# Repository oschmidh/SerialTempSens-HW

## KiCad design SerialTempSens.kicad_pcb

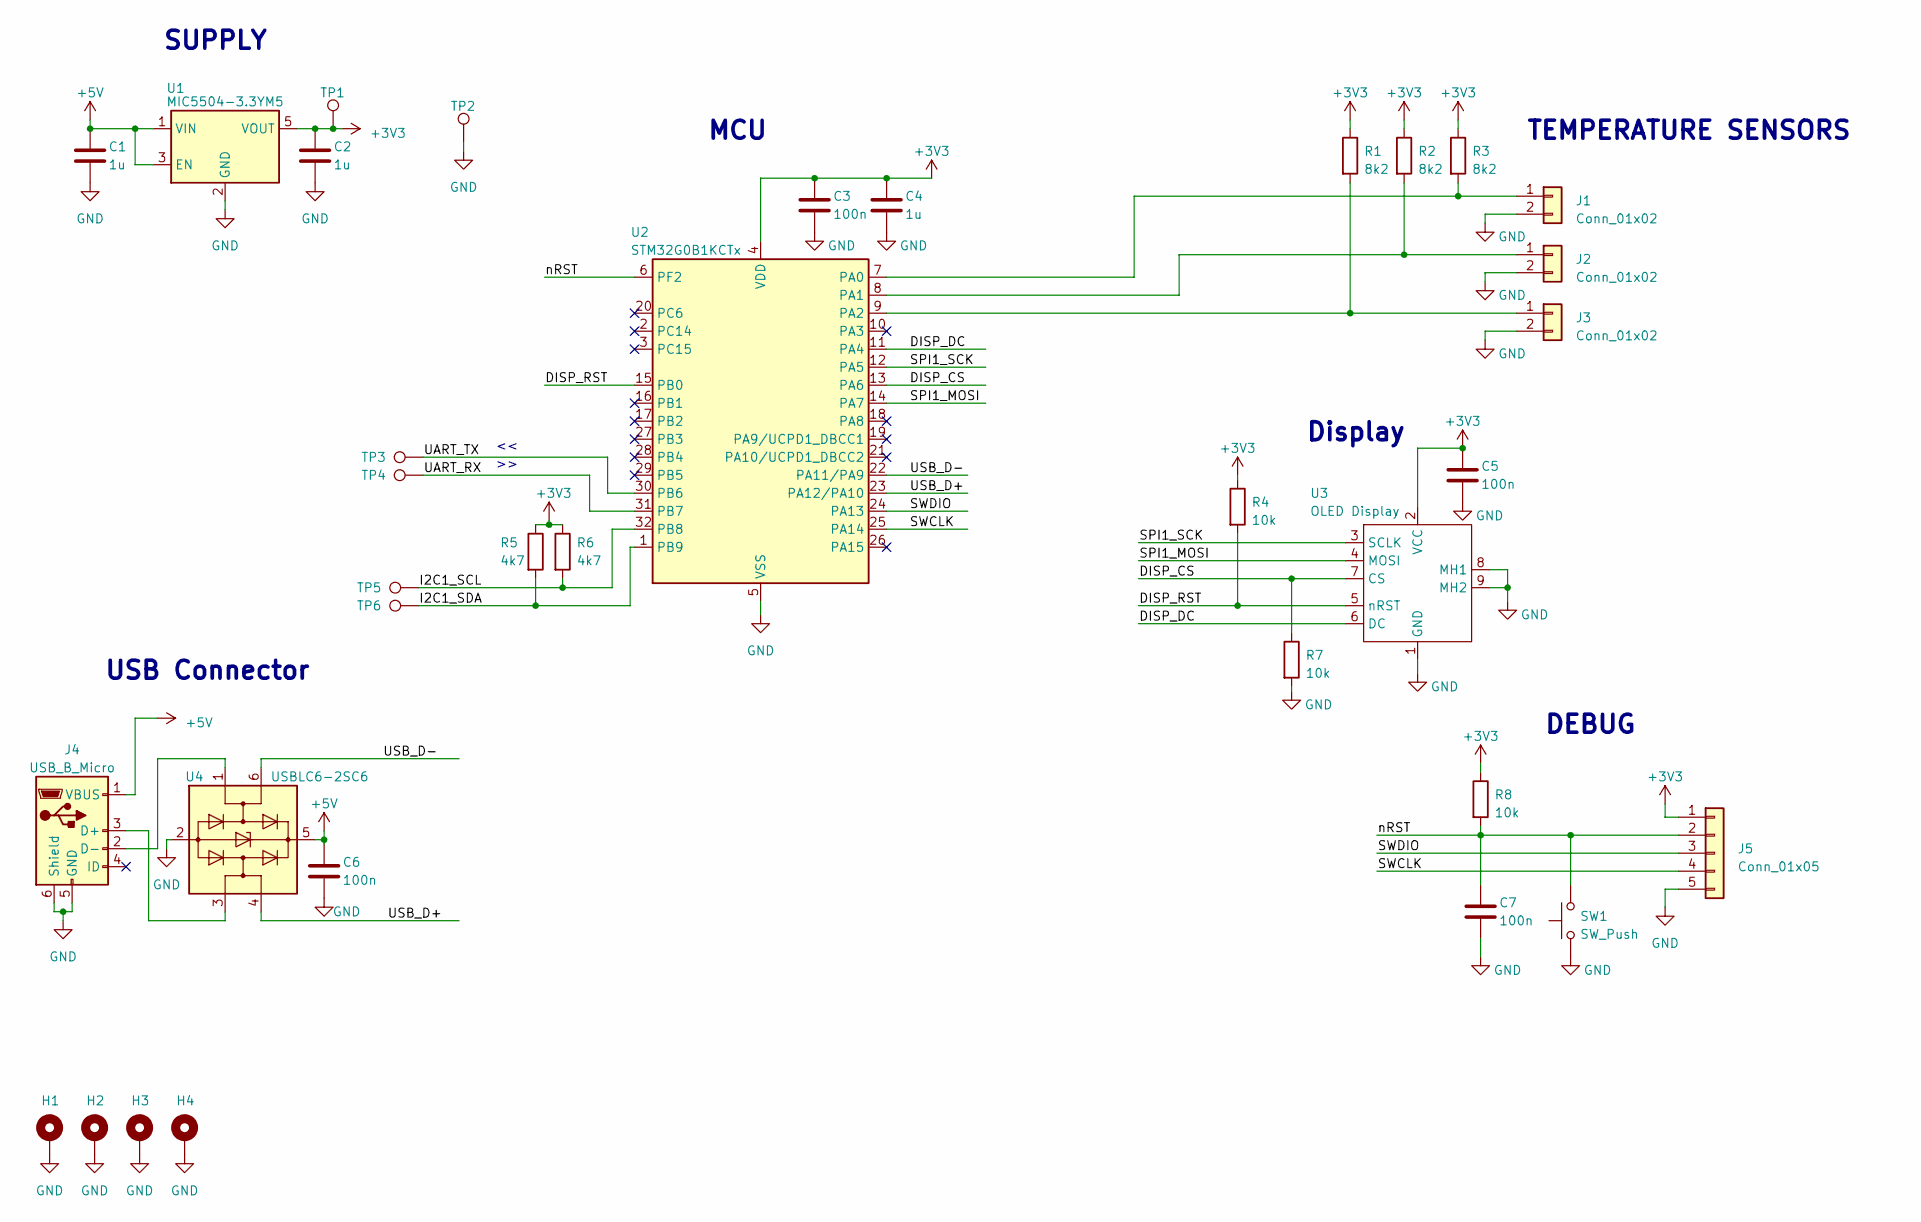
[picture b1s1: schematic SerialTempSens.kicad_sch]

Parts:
C1, C2, C4: 1u; C_1206_3216Metric_Pad1.33x1.80mm_HandSolder
C3, C6: 100n; C_0603_1608Metric_Pad1.08x0.95mm_HandSolder; LCSC C14663
C5, C7: 100n; C_0603_1608Metric_Pad1.08x0.95mm_HandSolder
H1, H2, H3, H4: MountingHole_Pad; MountingHole_2.7mm_M2.5_ISO7380_Pad
J1, J2, J3: Conn_01x02; PinHeader_1x02_P2.54mm_Horizontal
J4: USB_B_Micro; USB_Micro-B_Amphenol_10118194_Horizontal; LCSC C132563
J5: Conn_01x05; Molex_PicoBlade_53261-0571_1x05-1MP_P1.25mm_Horizontal
R1, R2, R3: 8k2; R_0603_1608Metric_Pad0.98x0.95mm_HandSolder
R4, R7, R8: 10k; R_0603_1608Metric_Pad0.98x0.95mm_HandSolder
R5, R6: 4k7; R_0603_1608Metric_Pad0.98x0.95mm_HandSolder
SW1: SW_Push; SW_Push_1P1T_NO_CK_KMR2; LCSC C221675
TP1, TP2, TP3, TP4, TP5, TP6: TestPoint; TestPoint_Pad_D1.5mm
U1: MIC5504-3.3YM5; SOT-23-5; LCSC C3021093
U2: STM32G0B1KCTx; LQFP-32_7x7mm_P0.8mm; LCSC C3223248
U3: OLED Display; SMIH-05VDC-SL-C,OLED_DISPLAY,128x64
U4: USBLC6-2SC6; SOT-23-6

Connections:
+3V3: C2.1, C3.1, C4.1, C5.1, J5.1, R1.1, R2.1, R3.1, R4.1, R5.1, R6.1, R8.1, TP1.1, U1.5 (VOUT), U2.4 (VDD), U3.2 (VCC)
+5V: C1.1, C6.1, J4.1 (VBUS), U1.1 (VIN), U1.3 (EN), U4.5 (VBUS)
/DISP_CS: R7.1, U2.13 (PA6), U3.7 (CS)
/DISP_DC: U2.11 (PA4), U3.6 (DC)
/DISP_RST: R4.2, U2.15 (PB0), U3.5 (nRST)
/I2C1_SCL: R6.2, TP5.1, U2.32 (PB8)
/I2C1_SDA: R5.2, TP6.1, U2.1 (PB9)
/SPI1_MOSI: U2.14 (PA7), U3.4 (MOSI)
/SPI1_SCK: U2.12 (PA5), U3.3 (SCLK)
/SWCLK: J5.4, U2.25 (PA14)
/SWDIO: J5.3, U2.24 (PA13)
/UART_RX: TP4.1, U2.31 (PB7)
/UART_TX: TP3.1, U2.30 (PB6)
/USB_D+: U2.23 (PA12/PA10), U4.4 (I/O2)
/USB_D-: U2.22 (PA11/PA9), U4.6 (I/O1)
/nRST: C7.1, J5.2, R8.2, SW1.2, U2.6 (PF2)
GND: C1.2, C2.2, C3.2, C4.2, C5.2, C6.2, C7.2, H1.1, H2.1, H3.1, H4.1, J1.2, J2.2, J3.2, J4.5 (GND), J4.6 (Shield), J5.5, R7.2, SW1.1, TP2.1, U1.2 (GND), U2.5 (VSS), U3.1 (GND), U3.8 (MH1), U3.9 (MH2), U4.2 (GND)
unnamed: J1.1, R3.2, U2.7 (PA0)
unnamed: J2.1, R2.2, U2.8 (PA1)
unnamed: J3.1, R1.2, U2.9 (PA2)
unnamed: J4.3 (D+), U4.3 (I/O2)
unnamed: J4.2 (D-), U4.1 (I/O1)

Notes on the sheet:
DEBUG
USB Connector
MCU
SUPPLY
Display
TEMPERATURE SENSORS

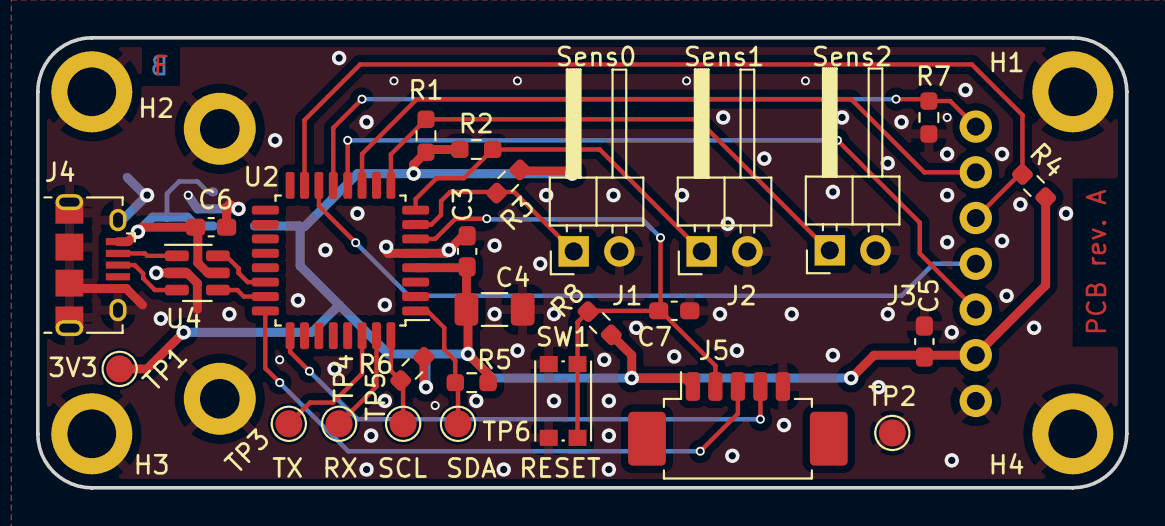
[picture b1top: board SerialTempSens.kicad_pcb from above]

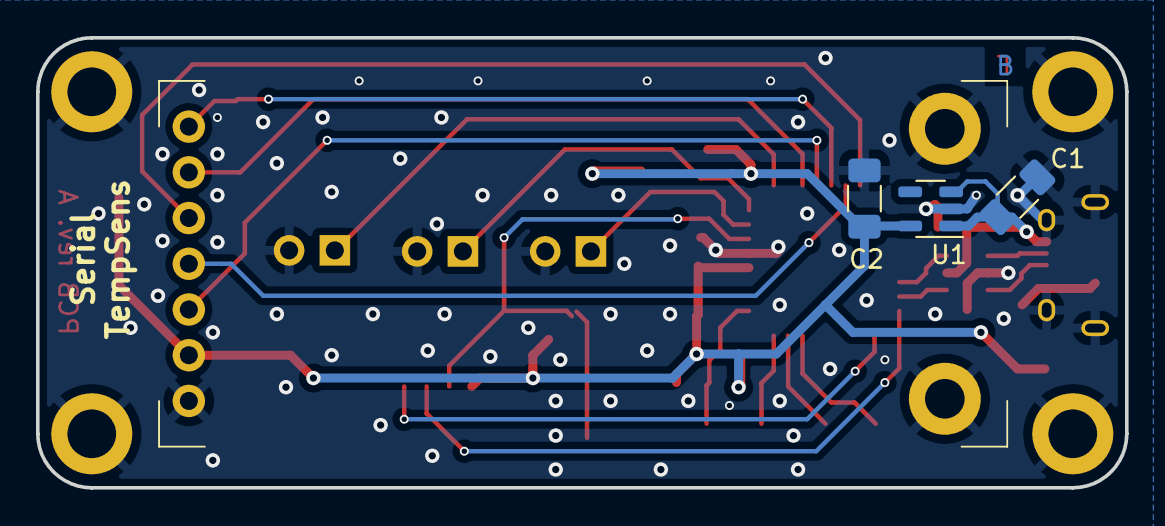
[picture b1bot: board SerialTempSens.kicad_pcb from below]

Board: 2 copper layers, 60.5 x 25.0 mm, 35 parts (4 on the bottom side), 22 nets.

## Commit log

2023-10-30 Create project
2023-10-30 Add personal library
2023-10-30 Fix library path
2023-10-30 Rename project, update footprint
2024-03-09 Cleanup fab layers for better layout diagram
